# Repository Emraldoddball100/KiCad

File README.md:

# KiCad
PCB designs
Novel implementation of an IR Sensor on KiCAD

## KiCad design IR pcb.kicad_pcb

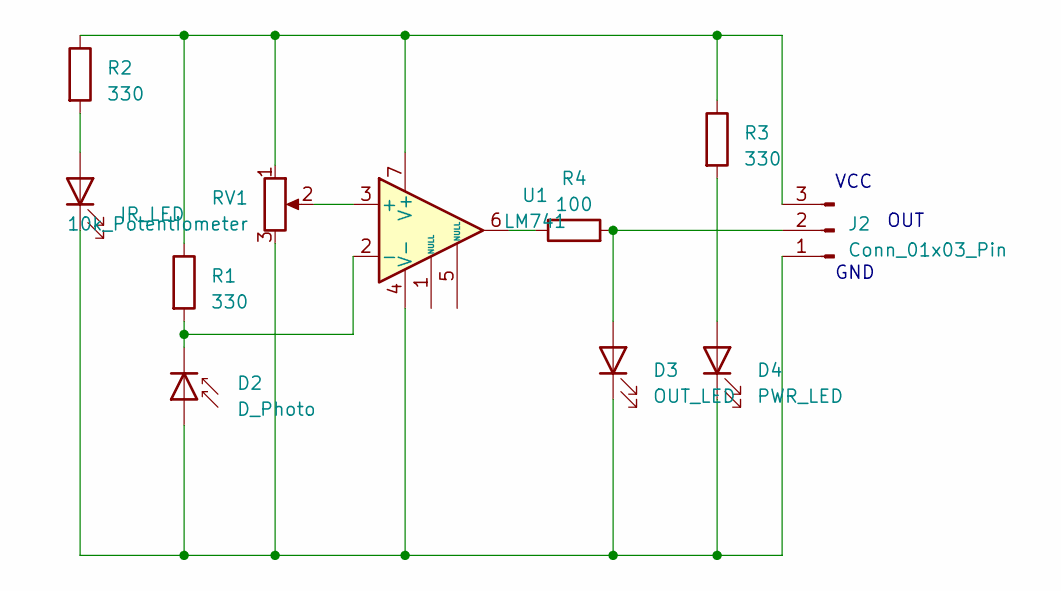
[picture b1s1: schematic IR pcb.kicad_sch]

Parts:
D1: IR_LED; LED_D5.0mm_Horizontal_O1.27mm_Z3.0mm
D2: D_Photo; LED_D5.0mm_Horizontal_O1.27mm_Z3.0mm
D3: OUT_LED; LED_0805_2012Metric_Pad1.15x1.40mm_HandSolder
D4: PWR_LED; LED_0805_2012Metric_Pad1.15x1.40mm_HandSolder
J2: Conn_01x03_Pin; PinHeader_1x03_P2.54mm_Horizontal
R1, R2, R3: 330; R_0805_2012Metric
R4: 100; R_0805_2012Metric
RV1: 10k_Potentiometer; Potentiometer_ACP_CA9-V10_Vertical
U1: LM741; TSSOP-8_3x3mm_P0.65mm

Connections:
unnamed: D1.2 (A), R2.2
unnamed: D1.1 (K), D2.2 (A), D3.1 (K), D4.1 (K), J2.1, RV1.3, U1.4 (V-)
unnamed: D2.1 (K), R1.2, U1.2 (-)
unnamed: D3.2 (A), J2.2, R4.2
unnamed: D4.2 (A), R3.2
unnamed: J2.3, R1.1, R2.1, R3.1, RV1.1, U1.7 (V+)
unnamed: R4.1, U1.6
unnamed: RV1.2, U1.3 (+)

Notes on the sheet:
VCC
OUT
GND

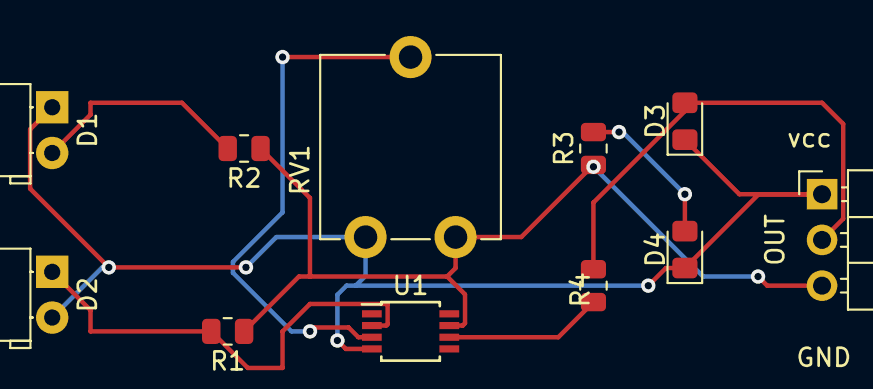
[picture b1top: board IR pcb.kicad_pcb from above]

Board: 2 copper layers, 11 parts (0 on the bottom side), 8 nets.

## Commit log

2023-04-30 IR Sensor PCB design
